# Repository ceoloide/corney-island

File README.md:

<h1 align="center">C O R N E Y &nbsp; I S L A N D</h1>

<p align="center">A Corne-compatible split keyboard, defined in code with <a href="https://github.com/ergogen/ergogen">Ergogen</a> and automatically routed with <a href="https://github.com/freerouting/freerouting">Freerouting</a>.</p>

<p align="center">
  
</p>

Corney Island is a **42-key column-staggered split keyboard** with wired and wireless PCB variants. It takes inspiration from [foostan’s Corne (crkbd)](https://github.com/foostan/crkbd) and [soundmonster’s Samoklava](https://github.com/soundmonster/samoklava), and brings the layout, electronics, plates, and case geometry together in a programmable design.

The board is **pin-compatible with crkbd v3 QMK firmware**, and its layout is **dimensionally 100% compatible with crkbd v3 plates and cases**. The wireless firmware is built on ZMK.

▲ My wireless **v0.1** build, which has been my daily driver since **January 2024**, with no known issues to report. The current design in this repository is **v0.4**.

***

## LAYOUT

Each half has a 3 × 6 finger matrix and three thumb keys. The current **v0.4** configuration uses **Choc v2 switches**, hot-swap footprints, and **19 mm horizontal and vertical key spacing**.

The source also contains MX and Choc v1 presets. These are customization starting points: changing a preset changes board dimensions, and switch footprints parameters may need adjusting. The crkbd v3 dimensional compatibility statement applies to the current MX spacing layout.

***

## PCB

Both variants use a reversible PCB design with a Pro Micro / nice!nano-style controller footprint.

| | Wired | Wireless |
| --- | --- | --- |
| Board | `corney_island` | `corney_island_wireless` |
| Firmware | crkbd v3-compatible QMK | ZMK shield linked below |
| Display footprint | SSD1306 OLED | nice!view |
| Connection between halves | TRRS | Wireless |
| Lighting footprints | Per-key RGB and six underglow LEDs per half | None |
| Additional hardware | Through-hole reset switch | Side-mounted power and reset switches; JST-PH battery connector |

### Wired

| Top | Bottom |
| --- | --- |
|  |  |

### Wireless

| Top | Bottom |
| --- | --- |
|  |  |

The [KiCad files](pcbs/) and [Gerber archives](gerbers/) are included in this repository. See the [generation and validation guide](docs/ergogen.md#routing-and-fabrication) before producing new fabrication files.

***

## CASE & PLATES

The board layout is dimensionally **100% compatible with crkbd v3 plates and cases**, so you can use the existing Corne v3 ecosystem.

This repository also includes its own generated parts:

- [Bottom tray](cases/): JSCAD source and a printable STL.
- [Switch plate](outlines/frontplate.svg): [SVG](outlines/frontplate.svg), [DXF](outlines/frontplate.dxf), and [KiCad PCB](pcbs/frontplate.kicad_pcb).
- [Backplate](outlines/backplate.svg): [SVG](outlines/backplate.svg), [DXF](outlines/backplate.dxf), and [KiCad PCB](pcbs/backplate.kicad_pcb).
- [Controller overlay](outlines/controller_overlay.svg): [SVG](outlines/controller_overlay.svg), [DXF](outlines/controller_overlay.dxf), and [KiCad PCB](pcbs/controller_overlay.kicad_pcb).

Controller, display, socket, and battery heights still determine the clearance needed for a particular build.

***

## MY BUILD

The wireless keyboard pictured above uses:

| Part | Hardware |
| --- | --- |
| Controller | [nice!nano v2](https://typeractive.xyz/products/nice-nano) |
| Display | [nice!view](https://typeractive.xyz/products/nice-view) |
| Controller sockets | [Typeractive EZ-Solder machine sockets and headers](https://typeractive.xyz/products/ez-machine-sockets-and-headers) |
| Battery | [Typeractive 3.7 V, 110 mAh 301230 lithium-ion battery](https://typeractive.xyz/products/lithium-battery-110mah) |
| Plates & Hardware | [LittleKeyboards Corne Analyst Case](https://www.littlekeyboards.com/collections/corne-cases/products/corne-analyst-case) |
| Switches | [Lofree Ghost, Choc v2 POM](https://www.lofree.co/products/lofree-ghost-switches) |
| Keycaps | [XVX Low Profile PBT, white-on-black](https://www.amazon.com/dp/B0CBMQH8H8) |

***

## MADE WITH ERGOGEN

**The board is defined programmatically in [`ergogen/config.yaml`](ergogen/config.yaml).** That file describes key spacing, column stagger, thumb positions, mounting holes, board and plate outlines, footprint placement, electrical nets, and the bottom tray. The wired and wireless PCBs share a common definition and add their own peripherals.

[Ergogen](https://github.com/ergogen/ergogen) turns this configuration into KiCad PCBs, SVG/DXF outlines, and JSCAD case geometry. The local build converts the case to STL; a separate KiCad, Freerouting, and KiBot pipeline routes the boards, checks them, and exports manufacturing files.

To modify the design, edit the YAML and regenerate the outputs. Layout dimensions and component positions can be expressed as variables and relationships, keeping the different parts of the keyboard tied to the same source.

The button opens the GitHub version of this project in [Ergogen’s web editor](https://github.com/ergogen/ergogen-gui). See the [generation guide](docs/ergogen.md) for local setup, configuration changes, and the routing workflow.

***

## FIRMWARE

### Wired · QMK

Corney Island is **pin-compatible with crkbd v3 QMK firmware**. Use the crkbd v3 configuration appropriate to your controller and enable the peripherals fitted to your board. Choose firmware for the controller you installed.

### Wireless · ZMK

The wireless variant has its own shield repository:

**[Corney Island Wireless ZMK shield](https://github.com/ceoloide/corney-island-wireless-zmk-shield)**

Use that repository as the starting point for the wireless firmware configuration.

***

## CREDITS

- [Corne / crkbd](https://github.com/foostan/crkbd) by [foostan](https://github.com/foostan): the layout and compatibility foundation.
- [Samoklava](https://github.com/soundmonster/samoklava) by [soundmonster](https://github.com/soundmonster): inspiration for this project and use of Freerouting.
- [Ergogen](https://github.com/ergogen/ergogen) and [Ergogen GUI](https://github.com/ergogen/ergogen-gui): the keyboard generator and best Discord community.
- [ceoloide’s Ergogen footprints](https://github.com/ceoloide/ergogen-footprints): the footprint library included as a Git submodule.
- [TOTEM](https://github.com/GEIGEIGEIST/TOTEM) by [GEIGEIGEIST](https://github.com/GEIGEIGEIST): inspiration for this documentation’s structure.

***

## LICENSE

[MIT](LICENSE) · Copyright © 2024 Marco Massarelli.

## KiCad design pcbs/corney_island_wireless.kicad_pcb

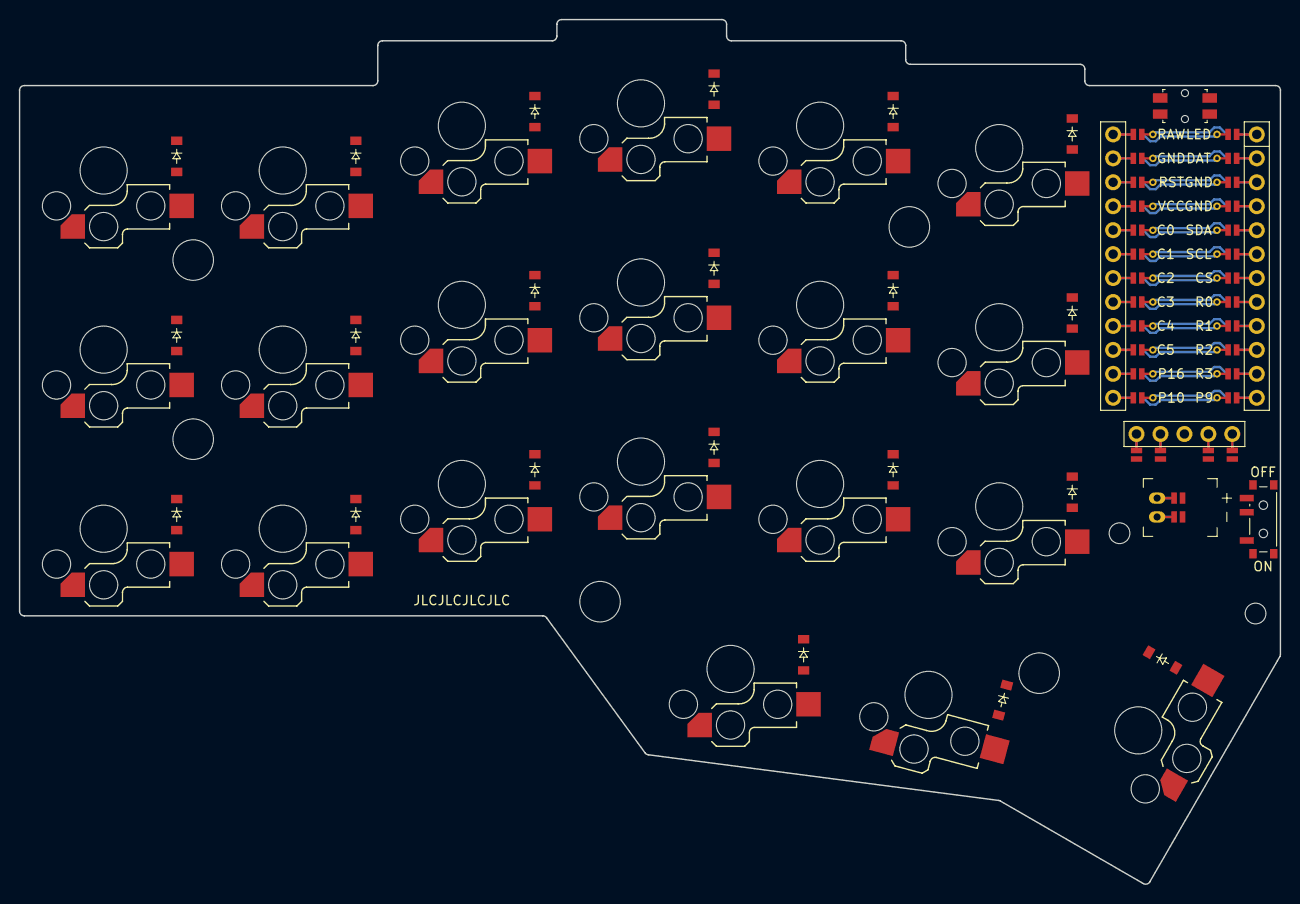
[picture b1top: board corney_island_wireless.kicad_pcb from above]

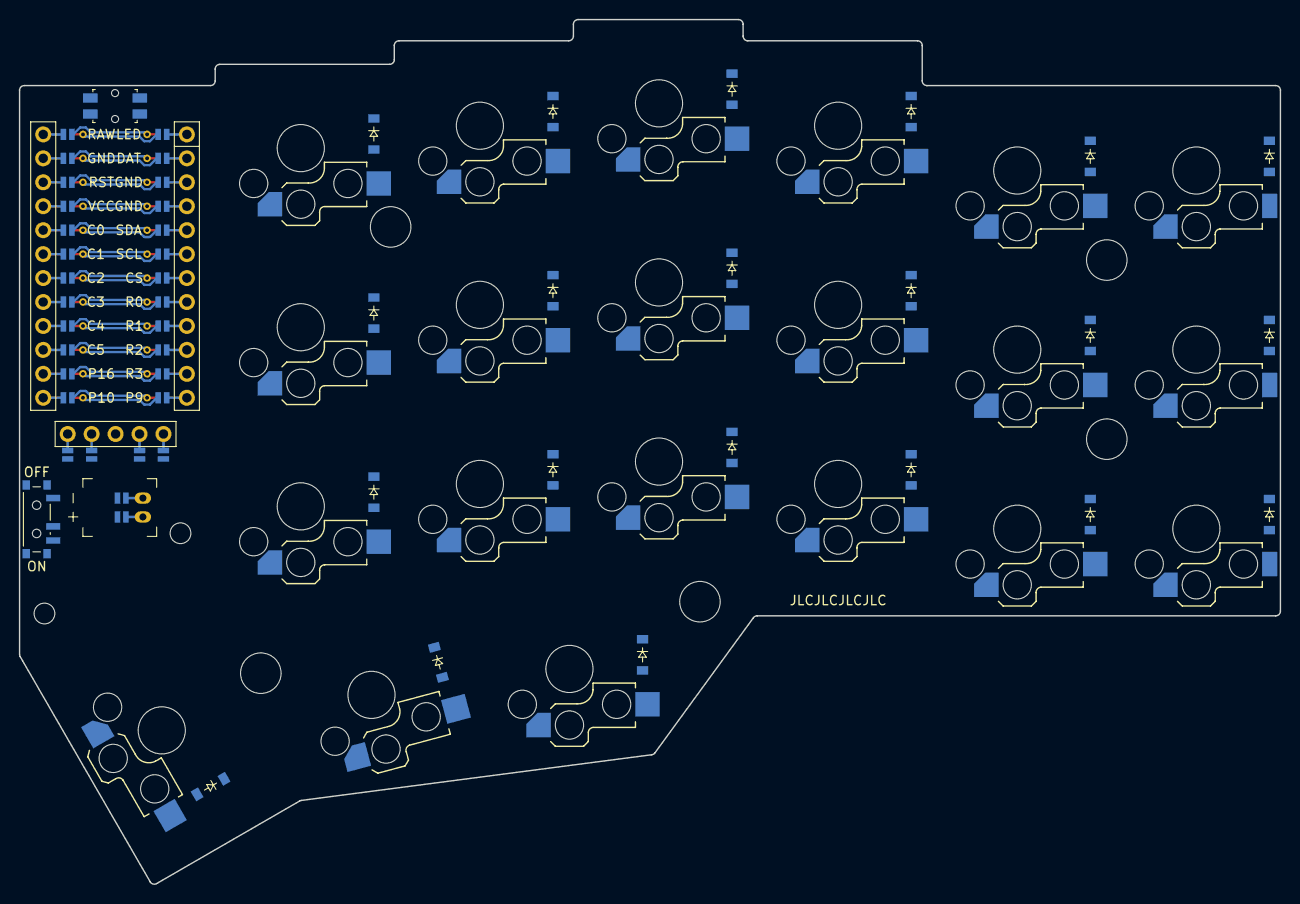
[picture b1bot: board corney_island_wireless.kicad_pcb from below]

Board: 2 copper layers, 133.8 x 91.7 mm, 75 parts (42 on the bottom side), 45 nets.

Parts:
D1, D2, D3, D4, D5, D6, D7, D8, D9, D10, D11, D12, D13, D14, D15, D16, D17, D18, D19, D20, D21, D22, D23, D24, D25, D26, D27, D28, D29, D30, D31, D32, D33, D34, D35, D36, D37, D38, D39, D40, D41, D42: diode_tht_sod123
DISP1: display_nice_view
JST1: battery_connector_jst_ph_2
MCU1: mcu_nice_nano
MH1, MH2, MH3, MH4, MH5, MH6, MH7: mounting_hole_npth
PWR1: power_switch_smd_side
RST1: reset_switch_smd_side
S1, S2, S3, S4, S5, S6, S7, S8, S9, S10, S11, S12, S13, S14, S15, S16, S17, S18, S19, S20, S21: switch_choc_v1_v2

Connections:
BAT_P: JST1.1, PWR1.1, PWR1.3
C0: MCU1.120, S1.1, S2.1, S3.1
C1: MCU1.119, S4.1, S5.1, S6.1
C2: MCU1.118, S7.1, S8.1, S9.1
C3: MCU1.117, S10.1, S11.1, S12.1, S19.1
C4: MCU1.116, S13.1, S14.1, S15.1, S20.1
C5: MCU1.115, S16.1, S17.1, S18.1, S21.1
CS: DISP1.10, DISP1.20, MCU1.107
DISP1_1: DISP1.1, DISP1.14, DISP1.27
DISP1_2: DISP1.2, DISP1.15, DISP1.26
DISP1_4: DISP1.4, DISP1.16, DISP1.25
DISP1_5: DISP1.5, DISP1.17, DISP1.24
GND: DISP1.11, DISP1.21, JST1.2, MCU1.103, MCU1.104, MCU1.123, RST1.1, RST1.3
JST1_1: JST1.11, JST1.21, JST1.31
JST1_2: JST1.12, JST1.22, JST1.32
R0: D3.1, D6.1, D9.1, D12.1, D15.1, D18.1, D24.1, D27.1, D30.1, D33.1, D36.1, D39.1, MCU1.108
R1: D2.1, D5.1, D8.1, D11.1, D14.1, D17.1, D23.1, D26.1, D29.1, D32.1, D35.1, D38.1, MCU1.109
R2: D1.1, D4.1, D7.1, D10.1, D13.1, D16.1, D22.1, D25.1, D28.1, D31.1, D34.1, D37.1, MCU1.110
R3: D19.1, D20.1, D21.1, D40.1, D41.1, D42.1, MCU1.111
RAW: MCU1.124, PWR1.2
RST: MCU1.122, RST1.2, RST1.4
SCL: DISP1.12, DISP1.22, MCU1.106
SDA: DISP1.13, DISP1.23, MCU1.105
VCC: DISP1.3, MCU1.121
far_home_B: D21.2, S21.2
index_bottom_B: D13.2, S13.2
index_home_B: D14.2, S14.2
index_top_B: D15.2, S15.2
inner_bottom_B: D16.2, S16.2
inner_home_B: D17.2, S17.2
inner_top_B: D18.2, S18.2
mid_home_B: D20.2, S20.2
middle_bottom_B: D10.2, S10.2
middle_home_B: D11.2, S11.2
middle_top_B: D12.2, S12.2
near_home_B: D19.2, S19.2
outer_bottom_B: D1.2, S1.2
outer_home_B: D2.2, S2.2
outer_top_B: D3.2, S3.2
pinky_bottom_B: D4.2, S4.2
pinky_home_B: D5.2, S5.2
pinky_top_B: D6.2, S6.2
ring_bottom_B: D7.2, S7.2
ring_home_B: D8.2, S8.2
ring_top_B: D9.2, S9.2

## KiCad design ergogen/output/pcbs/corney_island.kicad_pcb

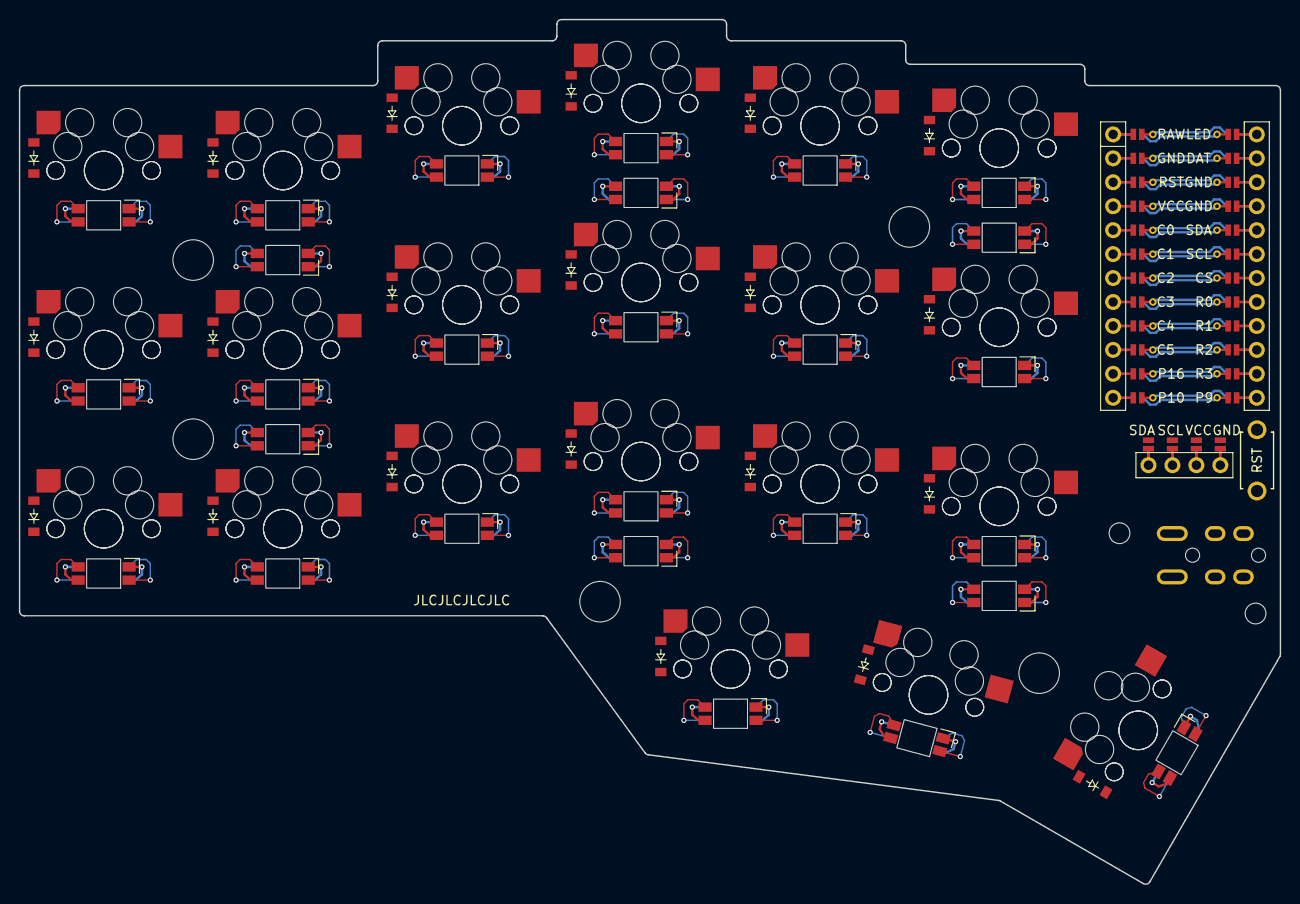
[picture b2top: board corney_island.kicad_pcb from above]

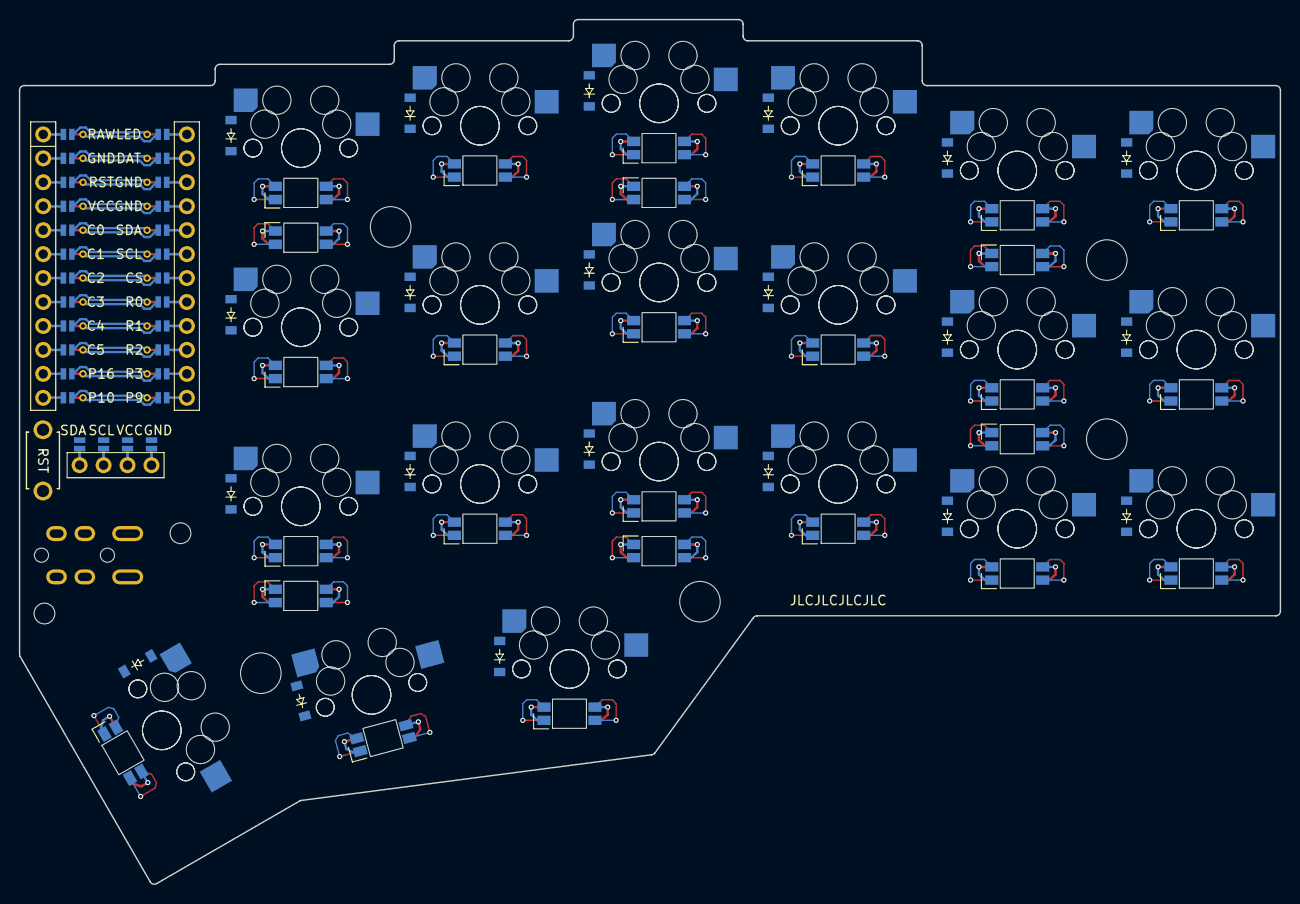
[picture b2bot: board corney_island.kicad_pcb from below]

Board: 2 copper layers, 133.8 x 91.7 mm, 122 parts (69 on the bottom side), 101 nets.

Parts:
D1, D2, D3, D4, D5, D6, D7, D8, D9, D10, D11, D12, D13, D14, D15, D16, D17, D18, D19, D20, D21, D22, D23, D24, D25, D26, D27, D28, D29, D30, D31, D32, D33, D34, D35, D36, D37, D38, D39, D40, D41, D42: diode_tht_sod123
DISP1: display_ssd1306
LED1, LED2, LED3, LED4, LED5, LED6, LED7, LED8, LED9, LED10, LED11, LED12, LED13, LED14, LED15, LED16, LED17, LED18, LED19, LED20, LED21: led_SK6812mini-e (per-key, reversible)
LED22, LED23, LED24, LED25, LED26, LED27: led_SK6812mini-e (underglow, reversible)
MCU1: mcu_nice_nano
MH1, MH2, MH3, MH4, MH5, MH6, MH7: mounting_hole_npth
RST1: reset_switch_tht_top
S1, S2, S3, S4, S5, S6, S7, S8, S9, S10, S11, S12, S13, S14, S15, S16, S17, S18, S19, S20, S21, S22, S23, S24, S25, S26, S27, S28, S29, S30, S31, S32, S33, S34, S35, S36, S37, S38, S39, S40, S41, S42: switch_mx
TRRS1: trrs_pj320a (reversible, symmetric)

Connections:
C0: MCU1.120, S1.1, S2.1, S3.1, S22.1, S23.1, S24.1
C1: MCU1.119, S4.1, S5.1, S6.1, S25.1, S26.1, S27.1
C2: MCU1.118, S7.1, S8.1, S9.1, S28.1, S29.1, S30.1
C3: MCU1.117, S10.1, S11.1, S12.1, S19.1, S31.1, S32.1, S33.1, S40.1
C4: MCU1.116, S13.1, S14.1, S15.1, S20.1, S34.1, S35.1, S36.1, S41.1
C5: MCU1.115, S16.1, S17.1, S18.1, S21.1, S37.1, S38.1, S39.1, S42.1
DAT: MCU1.102, TRRS1.3
DISP1_1: DISP1.1, DISP1.10, DISP1.23
DISP1_2: DISP1.2, DISP1.11, DISP1.22
DISP1_3: DISP1.3, DISP1.12, DISP1.21
DISP1_4: DISP1.4, DISP1.13, DISP1.20
GND: DISP1.14, DISP1.24, LED1.3, LED2.3, LED3.3, LED4.3, LED5.3, LED6.3, LED7.3, LED8.3, LED9.3, LED10.3, LED11.3, LED12.3, LED13.3, LED14.3, LED15.3, LED16.3, LED17.3, LED18.3, LED19.3, LED20.3, LED21.3, LED22.3, LED23.3, LED24.3, LED25.3, LED26.3, LED27.3, MCU1.103, MCU1.104, MCU1.123, RST1.2, TRRS1.2
LED: LED22.4, MCU1.101
LED_1: LED16.4, LED21.2
LED_2: LED16.2, LED17.4
LED_3: LED17.2, LED18.4
LED_4: LED15.4, LED18.2
LED_5: LED14.4, LED15.2
LED_6: LED13.4, LED14.2
LED_7: LED13.2, LED20.4
LED_8: LED19.4, LED20.2
LED_9: LED10.4, LED19.2
LED_10: LED10.2, LED11.4
LED_11: LED11.2, LED12.4
LED_12: LED9.4, LED12.2
LED_13: LED8.4, LED9.2
LED_14: LED7.4, LED8.2
LED_15: LED4.4, LED7.2
LED_16: LED4.2, LED5.4
LED_17: LED5.2, LED6.4
LED_18: LED3.4, LED6.2
LED_19: LED2.4, LED3.2
LED_20: LED1.4, LED2.2
MCU1_1: MCU1.1, MCU1.24
MCU1_2: MCU1.2, MCU1.23
MCU1_3: MCU1.3, MCU1.22
MCU1_4: MCU1.4, MCU1.21
MCU1_5: MCU1.5, MCU1.20
MCU1_6: MCU1.6, MCU1.19
MCU1_7: MCU1.7, MCU1.18
MCU1_8: MCU1.8, MCU1.17
MCU1_9: MCU1.9, MCU1.16
MCU1_10: MCU1.10, MCU1.15
MCU1_11: MCU1.11, MCU1.14
MCU1_12: MCU1.12, MCU1.13
R0: D3.1, D6.1, D9.1, D12.1, D15.1, D18.1, D24.1, D27.1, D30.1, D33.1, D36.1, D39.1, MCU1.108
R1: D2.1, D5.1, D8.1, D11.1, D14.1, D17.1, D23.1, D26.1, D29.1, D32.1, D35.1, D38.1, MCU1.109
R2: D1.1, D4.1, D7.1, D10.1, D13.1, D16.1, D22.1, D25.1, D28.1, D31.1, D34.1, D37.1, MCU1.110
R3: D19.1, D20.1, D21.1, D40.1, D41.1, D42.1, MCU1.111
RST: MCU1.122, RST1.1
SCL: DISP1.16, DISP1.26, MCU1.106
SDA: DISP1.17, DISP1.27, MCU1.105
ULED_1: LED22.2, LED23.4
ULED_2: LED23.2, LED24.4
ULED_3: LED24.2, LED25.4
ULED_4: LED25.2, LED26.4
ULED_5: LED26.2, LED27.4
ULED_6: LED21.4, LED27.2
VCC: DISP1.15, DISP1.25, LED1.1, LED2.1, LED3.1, LED4.1, LED5.1, LED6.1, LED7.1, LED8.1, LED9.1, LED10.1, LED11.1, LED12.1, LED13.1, LED14.1, LED15.1, LED16.1, LED17.1, LED18.1, LED19.1, LED20.1, LED21.1, LED22.1, LED23.1, LED24.1, LED25.1, LED26.1, LED27.1, MCU1.121, TRRS1.4
far_home_B: D21.2, S21.2
far_home_F: D42.2, S42.2
index_bottom_B: D13.2, S13.2
index_bottom_F: D34.2, S34.2
index_home_B: D14.2, S14.2
index_home_F: D35.2, S35.2
index_top_B: D15.2, S15.2
index_top_F: D36.2, S36.2
inner_bottom_B: D16.2, S16.2
inner_bottom_F: D37.2, S37.2
inner_home_B: D17.2, S17.2
inner_home_F: D38.2, S38.2
inner_top_B: D18.2, S18.2
inner_top_F: D39.2, S39.2
mid_home_B: D20.2, S20.2
mid_home_F: D41.2, S41.2
middle_bottom_B: D10.2, S10.2
middle_bottom_F: D31.2, S31.2
middle_home_B: D11.2, S11.2
middle_home_F: D32.2, S32.2
middle_top_B: D12.2, S12.2
middle_top_F: D33.2, S33.2
near_home_B: D19.2, S19.2
near_home_F: D40.2, S40.2
outer_bottom_B: D1.2, S1.2
outer_bottom_F: D22.2, S22.2
outer_home_B: D2.2, S2.2
outer_home_F: D23.2, S23.2
outer_top_B: D3.2, S3.2
outer_top_F: D24.2, S24.2
pinky_bottom_B: D4.2, S4.2
pinky_bottom_F: D25.2, S25.2
pinky_home_B: D5.2, S5.2
pinky_home_F: D26.2, S26.2
pinky_top_B: D6.2, S6.2
pinky_top_F: D27.2, S27.2
ring_bottom_B: D7.2, S7.2
ring_bottom_F: D28.2, S28.2
ring_home_B: D8.2, S8.2
ring_home_F: D29.2, S29.2
ring_top_B: D9.2, S9.2
ring_top_F: D30.2, S30.2

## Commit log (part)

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2023-06-15 Update choc v1 led position
2023-06-15 Fix wrong preset reference
2023-06-15 Rotate diode to align with Front switch pad
2023-06-15 Simplify sk6812mini-e silk screen
2023-06-15 Reduced silkscreen size further
2023-06-15 Add SMD toggle
2023-06-16 Update default nets
2023-06-16 Add courtyard
2023-06-16 Indent more
2023-06-16 Fix screw position and simplify shift values
2023-07-24 Fix inner underglow LED position
2023-07-24 Overhaul outlines making use of intersect
2023-07-24 Change to relative measures for helper points
2023-07-24 Add missing parametric measures
2023-07-24 Fix keycap and preview outlines
2023-07-24 Update GitHub Workflow to trigger for useful files
2023-07-28 Simplify the helper point definition
2023-08-13 Add nodemon to rebuild files on save
2023-08-13 Add parametrix NPTH footprint
2023-08-14 Update screw hole definition
2023-08-14 Update the diode to be optionally reversible
2023-08-14 Use helper points for screws
2023-08-15 Refresh generated files.
2023-08-27 Fix missing led net reference
2023-09-11 Fix duplicate thru-hole pads in reversible config
2023-09-11 Remove reference to kbd library
2023-09-26 Add initial support for KiBot and KiCad 7 CI/CD
2023-09-26 Split diode position on F and B layers
2023-09-27 Restored dynamic positioning of diodes
2023-09-30 Update build workflows to use KiBot (no autoroute)
2023-09-30 Fix list of boardcs in GitHub Action
2023-09-30 Add missing workspace reference
2023-09-30 Fix docker image reference
2023-10-02 Add infused-kim footprints submodule
2023-10-02 Switch to infused-kim nice-nano footprint
2023-10-02 Include submodules at checkout
2023-10-03 Fix per-key LED rotation on MX switches
2023-10-03 Add traces and vias to the LED footprint
2023-10-06 Add Freerouting rules file to improve autorouting
2023-10-06 Ignore Freerouting logs
2023-10-06 Update build.sh to use local Freerouting
2023-10-08 Update footprint with keepout and courtyard
2023-10-09 Add numbered pads and traces
2023-10-09 Add router footprints and switch traces / vias
2023-10-11 Fix LED orientation, traces, keepout
2023-10-11 Update traces with correct clearance values
2023-10-11 Update artifacts with latest unrouted build
2023-10-12 Update data net name to DAT
2023-10-12 Update artifacts with latest config + manual trace
2023-10-12 Fix usage of old data net name for TRRS
2023-10-12 Remove unused / redundant footprints
2023-10-12 Add JLCPCB production number text
2023-10-13 Fix pin 1 and 2 of the TRRS footprint
2023-10-15 Activate front copper
2023-10-15 Add nets and defaults
2023-10-15 Switch to Freerouting CLI
2023-10-15 Remove leading empty line
2023-10-15 Set start pass to 1 rather than 1001
2023-10-15 Renable autorouting in GitHub Actions
2023-10-15 Remove unused test PCB
2023-10-16 Add local nets functions
2023-10-16 Remove `(fill none)` not supported by KiCad 5
2023-10-16 Move switch hotswap routing
2023-10-16 Update OLED pad nets
2023-10-16 Re-enable autorouting in GitHub Actions
2023-10-16 Update assets
2023-10-16 Remove DRC checks from GitHub actions
2023-10-16 Switch routed board suffix to `_autorouted`
2023-10-17 Add freerouting rules and max passes
2023-10-17 Update KiBot to run DRC
2023-10-17 Update power / gnd Freerouting rules
2023-10-17 Add expected errors to KiBot filters
2023-10-17 Move MX traces to separate board
2023-10-17 Centralize trace widths
2023-10-17 Add partially routed PCB output
2023-10-17 Move switch traces to partially routed board
2023-10-17 Fix wrong KiBot file reference
2023-10-19 Add keepout and courtyard params to LEDs
2023-10-19 Add nix derivation for Freerouting
2023-10-19 Add nix-shell configuration
2023-10-19 Switch autorouting to nix-shell wrapper
2023-10-19 Switch to nix-shell wrapper of Freerouting 1.7.0
2023-10-19 Reorganize build script
2023-10-19 Bump node version in GitHub Actions to v18
2023-10-19 Update NPM packages
2023-10-19 Add back bash entry point
2023-10-20 Build Freerouting at HEAD
2023-10-21 Add TRRS custom footprint
2023-10-23 Replace screw holes with spacer holes
2023-10-23 Add the ability to set via size and drill
2023-10-23 Make use of via size and drill for LED
2023-10-23 Moved SDA / SCL pins to I2C pins
2023-10-24 Ignore PCBs starting with `_`
2023-10-24 Move underglow to helper points
2023-10-24 Update Freerouting rules to use smaller vias
2023-10-24 Remove smd toggle switch to use infused-kim's one
2023-10-24 Add initial wireless variant
2023-10-25 Add battery net to routing rules
2023-10-25 Revert to Freerouting CLI for GitHub action
2023-10-26 Increase via size to match JLCPCB min requirements
2023-10-26 Ignore logs when they are in freerouting dir
2023-10-27 Update files that trigger GitHub Actions
2023-10-29 Add reversible to the name (conditionally)
2023-10-29 Get rid of old display footprint
2023-10-30 Use Freerouting v1.9.0 instead of v1.8.0
2023-10-30 Remove partially routed board
2023-11-02 Remove attr from the footprint
2023-11-02 Revert back to p.rot to comply with Ergogen 4.0.4
2023-11-02 Switch to old net definition for Ergogen v4.0.4
2023-11-03 Update courtyard to include mated male conenctor
2023-11-05 Invert diode X position for choc switches
2023-11-11 Update reset button postition
2023-11-19 Update JST battery connector footprint
2023-11-19 Fix reversible pad polarity
2023-11-19 Update wireless footprints positions
2023-11-19 Update build.sh to include wireless
2023-11-21 Fix exclude for Freerouting log config
2023-11-21 Add chown command to fix root owner
2023-11-21 Fix wrong Freerouting parameter
2023-11-21 Add rebuild script for quick iterations
2023-11-21 Fix wrong local net for jumper pad
2023-11-21 Add battery connector nets
2023-11-22 Add traces to reversible pads
2023-11-22 Switch to infused-kim/nice_view display
2023-11-22 Fix on/off switch position for clearance violation
2023-11-23 Add Specctra SES file import from CLI
2023-11-23 Do not save project files after importing SES
2023-11-23 Switch to custom kicad_auto image
2023-11-23 Add Ergogen and Freerouting (cli and stable)
2023-11-24 Adjust version after importing SES
2023-11-25 Fix image references
2023-11-25 Fix wrong image reference
2023-11-25 Switch to last stable KiCad 7 version
2023-11-26 Add JS footprint extension to nodemon watch list
2023-11-26 Update silkscreen
2023-11-26 Add fork of infused-kim's footprints
2023-11-26 Fix footprint reference text
2023-11-27 Update nice!view position
2023-11-27 Revert to debug Ergogen build
2023-11-30 Move OLED slightly to make space for cables
2023-12-03 Add traces to reversible footprint
2024-01-03 Add Choc V2 footprint
2024-01-03 Add presets for Choc v2
2024-01-14 Fix pin polarity
2024-01-14 Expand courtyard to account for JST wires
2024-01-14 Move reference text
2024-01-14 Move battery connector
2024-01-14 Rotate battery connector
2024-01-15 Replace edge cut holes with footprint
2024-01-15 Add mention of LOFREE switches
2024-01-15 Add choc_v2 extends
2024-01-15 Reposition the reset switch
2024-01-15 Add support for oval stabilizer pads
2024-01-15 Separate out Choc v1 stabilizers
2024-01-15 Move a few components
2024-01-17 Update version
2024-01-17 Add reset button footprint for Typeractive.xyz component
2024-01-17 Update clearance values
2024-01-17 Make use of the correct power button
2024-01-17 Fix wrong ref to `reverse` parameter instead of `reversible`
2024-01-17 Add text footprint
2024-01-17 Switch to own text footprint
2024-01-17 Remove duplicate reference
2024-01-17 Renove extra parenthesis
2024-01-18 Use own power switch footprint
2024-01-18 Add option to invert switch behavior
2024-01-18 Invert behavior on back layer to maintain consistency
2024-01-18 Add choc_v1 central hole support
2024-01-18 Disable corner stab if `choc_v2_support` is false
2024-01-18 Rename choc v1 and v2 footprint file
2024-01-19 Add on/off silkscreen
2024-01-19 Added a note for the `side` parameter
2024-01-19 Slightly move diodes
2024-01-19 Move vias closer to the pads
2024-01-19 Update file header
2024-01-19 Add the ability to change size of vias
2024-01-21 Temporarily ignore unconnected pads, due to issues with Freerouting
2024-01-21 Add ability to use rectangular jumpers
2024-01-24 Change parameter from `reverse` to `reversible`
2024-01-24 Add documentation suggesting min outer pad width
2024-01-24 Update module name
2024-01-26 Rename `traces` with `include_traces` and add details in the footprint header
2024-01-26 Correct the minimum via size for JLCPCB
2024-01-28 Add license header and description
2024-01-28 Add license header and update notes
2024-01-28 Add datasheet and component reference
2024-01-28 Add license header and rename parameters
2024-01-28 Rename diode footprint name
2024-01-28 Add license header and reorder net params
2024-01-28 Add pinout and schematics link
2024-01-28 Update header
2024-01-28 Add header and rename parameters
2024-01-28 Update header and parameter names
2024-01-28 Change footprint name
2024-01-28 Overhaul footprint (header, params, name)
2024-01-28 Add header and rename params and file
2024-01-28 Update module name and font size
2024-01-29 Add file header
2024-01-29 Minor updates on the module name and header
2024-01-29 Rename and reorder trace params
2024-01-29 Add header and rename file and params
2024-01-29 Rename file to match new naming convention
2024-01-30 Update npm from 18 to 20
2024-01-30 Update `actions/checkout` to v4
2024-01-30 Update actions that depend on Node 16
2024-01-30 Hide solder paste in PCB images
2024-01-30 Update footprints dependencies
2024-01-30 Update footprint submodule
2024-02-26 Update footprint dependency
2024-02-26 Add 3D printed bottom case
2024-03-03 Update footprint library
2024-03-30 Update TRRS footprint pinout and module
2024-04-01 Switch to HTTPS for footprints submodule, to make it work with Codespaces
2024-04-01 Update build scripts to make use of KiCad Auto ki8 image (KiCad 8)
2024-04-01 Switch SES import to KiCad native
2024-04-01 Import SES through KiCad Auto ki8 (KiCad 8)
2024-04-02 Update footprint library and config
2024-04-05 Update footprints library and artifacts
2024-04-07 Update footprints library
2024-04-11 Remove deprecated fields
2024-04-11 Remove MCU instruction text (overlaps with reset switch)
2024-04-11 Switch to KiCad 8 PCB template and require Ergogen v4.1.0
2024-04-11 Update to Freerouting SNAPSHOT-20240405_140200
2024-04-11 Update Dockerfile to kicad_auto:ki8
2024-05-10 Update footprints library and NPM
2024-05-10 Use `ceoloide/switch_mx` instead of default ergogen
2024-05-11 Update KiBot configuration
2024-05-11 Add KiBot HTML DRC output
2024-05-29 Initial Typematrix from https://github.com/tbaumann/typematrix_split_ergogen/
2024-05-29 Deploy to pages
2024-05-29 deploy to pages version
2024-05-29 pages artifact name must match
2024-05-29 pages artifact name must match.
2024-05-29 Include README in pages
2024-05-29 front bottom vs top back
2024-05-30 Link build artifacts in README
2024-05-30 fix formatting
2024-06-06 Preview script
2024-06-07 Integration and watch mode
2024-06-07 Use prestets
2024-06-07 Just pimped
2024-06-07 Place Diodes on front
2024-10-01 Move controller to the top
2024-10-21 Start adopting freerouting-SNAPSHOT-20241021 which introduced CLI support
2024-10-21 Update ergogen-footprints library
2024-11-14 Switch to the latest Docker image
2024-11-14 Add back freerouting.rules
2024-12-04 Update @ceoloide's footprints library
2024-12-09 Update @ceoloide's footprint library
2025-09-04 Fix wrong artifact bundle name
    The final artifact bundle should be named `corney_island` instead `not_about_money`.
2025-09-16 Temporarily use snapshot image
2025-09-17 Update main config.yaml to v0.3 (Choc v2 POM variant)
2025-09-17 Fix output paths for images and gerbers
2025-09-17 Switch to a matrix strategy for the Build workflow
